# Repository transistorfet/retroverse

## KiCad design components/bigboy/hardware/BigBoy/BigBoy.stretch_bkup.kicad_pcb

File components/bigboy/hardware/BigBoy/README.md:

BigBoy
======

Status: Built & Tested but with design issues (see errata)

Latest: Rev. 1

### About

A generic card with an STM32H7 microcontroller on it that interfaces to the VME bus using GPIO.
I had intended to use it as a bus analyzer, but it's a bit too slow for the k30p CPU at 12.5MHz.

The logo is of [Bronson the Cat](https://www.instagram.com/iambronsoncat/?hl=en)

[Revision 1 Notes & Errata](revisions/BigBoy-rev1-errata.txt)

[Revision 1 Schematic](revisions/BigBoy-rev1.pdf)

[Revision 1 Gerbers](revisions/BigBoy-rev1.zip)

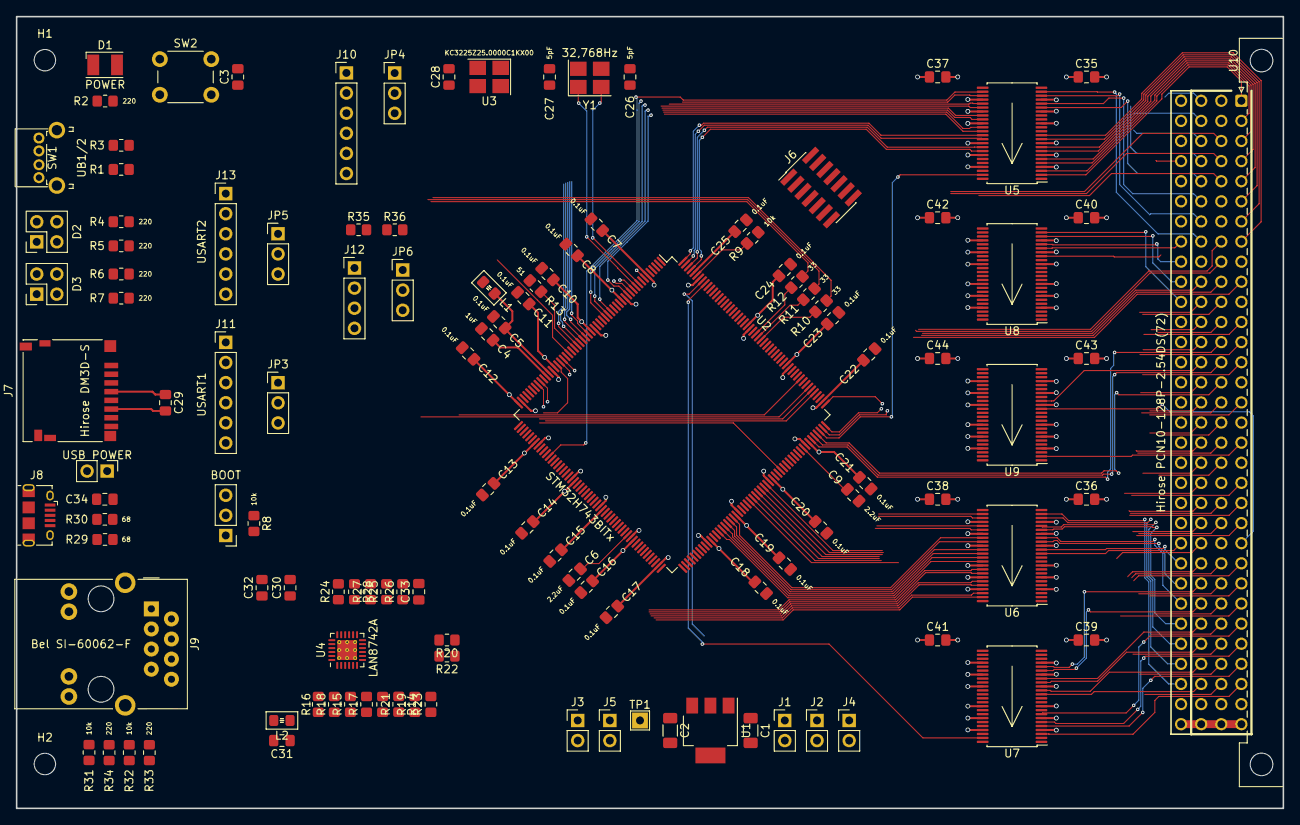
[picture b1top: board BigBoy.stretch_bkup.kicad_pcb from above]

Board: 4 copper layers, 160.0 x 100.0 mm, 120 parts (0 on the bottom side), 282 nets.

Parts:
C1, C2: 4.7uF; C_1206_3216Metric_Pad1.33x1.80mm_HandSolder
C3, C5, C7, C8, C10, C11, C12, C13, C14, C15, C16, C17, C18, C19, C20, C21, C22, C23, C24, C25, C28, C29, C30, C31, C32, C34, C35, C36, C37, C38, C39, C40, C41, C42, C43, C44: 0.1uF; C_0805_2012Metric_Pad1.18x1.45mm_HandSolder
C4: 1uF; C_0805_2012Metric_Pad1.18x1.45mm_HandSolder
C6, C9: 2.2uF; C_0805_2012Metric_Pad1.18x1.45mm_HandSolder
C26, C27: 5pF; C_0805_2012Metric_Pad1.18x1.45mm_HandSolder
C33: 10uF; C_0805_2012Metric_Pad1.18x1.45mm_HandSolder
D1: POWER; LED_PLCC-2_3.4x3.0mm_KA
D2: Dialight 5530188F; Dialight 553-0xxxF
D3: Dialight 5530177F; Dialight 553-0xxxF
H1, H2: MountingHole; MountingHole_2.7mm_M2.5_DIN965
J1, J2, J4: 5V; PinHeader_1x02_P2.54mm_Vertical
J3, J5: 3.3V; PinHeader_1x02_P2.54mm_Vertical
J6: Conn_ST_STDC14; PinHeader_2x07_P1.27mm_Vertical_SMD
J7: Hirose DM3D-S; microSD_HC_Hirose_DM3D-SF
J8: Amphenol 10118194-0001LF; USB_Micro-B_Amphenol_10118194_Horizontal
J9: Bel SI-60062-F; RJ45_Bel_SI-60062-F
J10: SPI2; PinHeader_1x06_P2.54mm_Vertical
J11: USART1; PinHeader_1x06_P2.54mm_Vertical
J12: I^{2}C1; PinHeader_1x04_P2.54mm_Vertical
J13: USART2; PinHeader_1x06_P2.54mm_Vertical
JP1: BOOT; PinHeader_1x03_P2.54mm_Vertical
JP2: USB POWER; PinHeader_1x02_P2.54mm_Vertical
JP3: USART1; PinHeader_1x03_P2.54mm_Vertical
JP4: SPI1; PinHeader_1x03_P2.54mm_Vertical
JP5: USART2; PinHeader_1x03_P2.54mm_Vertical
JP6: I^{2}C1; PinHeader_1x03_P2.54mm_Vertical
L1, L2: 600Ω @ 100MHz (MI0805K601R-10); Ferrite_0805_2012Metric_Pad1.15x1.40mm_BigPads
R1, R3, R8, R9, R14, R15, R16, R21, R22, R31, R32: 10k; R_0805_2012Metric_Pad1.20x1.40mm_HandSolder
R2, R4, R5, R6, R7, R33, R34: 220; R_0805_2012Metric_Pad1.20x1.40mm_HandSolder
R10, R11, R12, R17, R18, R19, R20: 33; R_0805_2012Metric_Pad1.20x1.40mm_HandSolder
R13: 51; R_0805_2012Metric_Pad1.20x1.40mm_HandSolder
R23: 1.5k; R_0805_2012Metric_Pad1.20x1.40mm_HandSolder
R24: 12.1k; R_0805_2012Metric_Pad1.20x1.40mm_HandSolder
R25, R26, R27, R28: 50; R_0805_2012Metric_Pad1.20x1.40mm_HandSolder
R29, R30: 68; R_0805_2012Metric_Pad1.20x1.40mm_HandSolder
R35, R36: 4.7k; R_0805_2012Metric_Pad1.20x1.40mm_HandSolder
SW1: UB1/2; E-Switch TL2243
SW2: ~{RESET}; SW_PUSH_6mm
TP1: 3.3V; TestPoint_THTPad_2.0x2.0mm_Drill1.0mm
U1: AP7361EA-33E-13; SOT-223
U2: STM32H743BITx; LQFP-208_28x28mm_P0.5mm
U3: KC3225Z25.0000C1KX00; Crystal_SMD_3225-4Pin_3.2x2.5mm_HandSoldering
U4: LAN8742A; VQFN-24-1EP_4x4mm_P0.5mm_EP2.5x2.5mm_ThermalVias
U5, U6, U7, U8, U9: 74ALVC16245DG; TSSOP-48_6.1x12.5mm_P0.5mm
U10: Hirose PCN10-128P-2.54DS(72); DIN41612_C_4x32_Male_Horizontal_THT
Y1: 32,768Hz; Crystal_SMD_3225-4Pin_3.2x2.5mm_HandSoldering

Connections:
+3.3V: C2.1, C7.1, C8.1, C10.1, C11.1, C12.1, C13.1, C14.1, C15.1, C16.1, C17.1, C18.1, C19.1, C20.1, C21.1, C22.1, C23.1, C24.1, C25.1, C28.1, C29.1, C30.1, C37.1, C38.1, C41.1, C42.1, C44.1, J3.1, J5.1, J6.3 (VCC), J7.4 (VDD), JP3.3 (B), JP4.3 (B), JP5.3 (B), JP6.3 (B), L1.2, L2.2, R1.1, R2.1, R3.1, R8.1, R9.1, R15.1, R16.1, R21.1, R22.1, R23.1, TP1.1, U1.3 (VO), U2.6 (VBAT), U2.15 (VDD), U2.26 (VDD), U2.39 (VDD), U2.52 (VDD), U2.59 (VDD), U2.73 (VDD), U2.83 (VDD), U2.94 (VDD), U2.103 (VDD), U2.115 (VDD), U2.124 (VDD), U2.137 (VDD33_USB), U2.150 (VDD), U2.158 (VDD), U2.171 (VDD), U2.185 (VDD), U2.204 (VDD), U3.1 (INH), U3.4 (VCC), U4.9 (VDDIO), U5.31 (VCCa), U5.42 (VCCa), U6.31 (VCCa), U6.42 (VCCa), U7.31 (VCCa), U7.42 (VCCa), U8.31 (VCCa), U8.42 (VCCa), U9.31 (VCCa), U9.42 (VCCa)
+5V: C1.1, C34.1, C35.2, C36.2, C39.2, C40.2, C43.2, J1.1, J2.1, J4.1, JP2.1 (A), JP3.1 (A), JP4.1 (A), JP5.1 (A), JP6.1 (A), U1.1 (VI), U5.7 (VCCb), U5.18 (VCCb), U6.7 (VCCb), U6.18 (VCCb), U7.7 (VCCb), U7.18 (VCCb), U8.7 (VCCb), U8.18 (VCCb), U9.7 (VCCb), U9.18 (VCCb), U10.a32 (+5V), U10.b32 (+5V), U10.c32 (+5V), U10.d1 (+5V), U10.d13 (+5V), U10.d32 (+5V)
/IO/RD+: J9.4 (RD+), R27.2, U4.23 (RXP)
/IO/RD-: J9.6 (RD-), R28.2, U4.22 (RXN)
/IO/TD+: J9.1 (TD+), R25.2, U4.21 (TXP)
/IO/TD-: J9.3 (TD-), R26.2, U4.20 (TXN)
AH_DIR: U2.54 (PA5), U6.24 (DIR2)
AL_DIR: U2.55 (PA6), U5.1 (DIR1), U5.24 (DIR2), U6.1 (DIR1)
CLK_25M: R13.2, U3.3 (CLK), U4.5 (XTAL1/CLKIN)
DH_DIR: U2.62 (PB1), U8.1 (DIR1), U8.24 (DIR2)
DL_DIR: U2.63 (PB2), U7.1 (DIR1), U7.24 (DIR2)
GND: C1.2, C2.2, C3.2, C4.1, C5.1, C6.2, C7.2, C8.2, C9.2, C10.2, C11.2, C12.2, C13.2, C14.2, C15.2, C16.2, C17.2, C18.2, C19.2, C20.2, C21.2, C22.2, C23.2, C24.2, C25.2, C26.2, C27.2, C28.2, C29.2, C30.2, C31.2, C32.2, C33.2, C34.2, C35.1, C36.1, C37.2, C38.2, C39.1, C40.1, C41.2, C42.2, C43.1, C44.2, D1.1 (K), D2.1 (A1), D2.3 (A2), D3.1 (A1), D3.3 (A2), J1.2, J2.2, J3.2, J4.2, J5.2, J6.5 (GND), J6.7 (GND), J6.11 (GNDDetect), J7.6 (VSS), J7.10 (SHIELD), J8.5 (GND), J8.6 (Shield), J9.8, J9.SH, J10.2, J11.6, J12.2, J13.6, JP1.3 (B), R14.2, R24.2, R31.2, R32.2, R33.2, R34.2, SW1.1 (C), SW1.3 (C), SW2.1, U1.2 (GND), U2.14 (VSS), U2.25 (VSS), U2.40 (VSSA), U2.51 (VSS), U2.60 (VSS), U2.72 (VSS), U2.82 (VSS), U2.93 (VSS), U2.114 (VSS), U2.125 (VSS), U2.136 (VSS), U2.149 (VSS), U2.170 (VSS), U2.184 (VSS), U2.202 (VSS), U3.2 (GND), U4.25 (VSS), U5.4 (GND), U5.10 (GND), U5.15 (GND), U5.21 (GND), U5.28 (GND), U5.34 (GND), U5.39 (GND), U5.45 (GND), U6.4 (GND), U6.10 (GND), U6.15 (GND), U6.21 (GND), U6.28 (GND), U6.34 (GND), U6.39 (GND), U6.45 (GND), U7.4 (GND), U7.10 (GND), U7.15 (GND), U7.21 (GND), U7.28 (GND), U7.34 (GND), U7.39 (GND), U7.45 (GND), U8.4 (GND), U8.10 (GND), U8.15 (GND), U8.21 (GND), U8.28 (GND), U8.34 (GND), U8.39 (GND), U8.45 (GND), U9.4 (GND), U9.10 (GND), U9.15 (GND), U9.21 (GND), U9.28 (GND), U9.34 (GND), U9.39 (GND), U9.45 (GND), U10.a9 (GND), U10.a11 (GND), U10.a15 (GND), U10.a17 (GND), U10.a19 (GND), U10.b20 (GND), U10.b23 (GND), U10.c9 (GND), U10.d2 (GND), U10.d12 (GND), U10.d22 (GND), U10.d31 (GND)
I2C_SCL: J12.3, R35.2, U2.198 (PB8)
I2C_SDA: J12.4, R36.2, U2.199 (PB9)
LA0: U2.200 (PE0), U7.47 (A0)
LA1: U2.201 (PE1), U7.46 (A1)
LA2: U2.1 (PE2), U7.44 (A2)
LA3: U2.2 (PE3), U7.43 (A3)
LA4: U2.3 (PE4), U7.41 (A4)
LA5: U2.4 (PE5), U7.40 (A5)
LA6: U2.5 (PE6), U7.38 (A6)
LA7: U2.79 (PE7), U7.37 (A7)
LA8: U2.80 (PE8), U7.36 (A8)
LA9: U2.81 (PE9), U7.35 (A9)
LA10: U2.84 (PE10), U7.33 (A10)
LA11: U2.85 (PE11), U7.32 (A11)
LA12: U2.86 (PE12), U7.30 (A12)
LA13: U2.87 (PE13), U7.29 (A13)
LA14: U2.88 (PE14), U7.27 (A14)
LA15: U2.89 (PE15), U7.26 (A15)
LA16: U2.16 (PF0), U8.47 (A0)
LA17: U2.17 (PF1), U8.46 (A1)
LA18: U2.18 (PF2), U8.44 (A2)
LA19: U2.22 (PF3), U8.43 (A3)
LA20: U2.23 (PF4), U8.41 (A4)
LA21: U2.24 (PF5), U8.40 (A5)
LA22: U2.27 (PF6), U8.38 (A6)
LA23: U2.28 (PF7), U8.37 (A7)
LA24: U2.29 (PF8), U8.36 (A8)
LA25: U2.30 (PF9), U8.35 (A9)
LA26: U2.31 (PF10), U8.33 (A10)
LA27: U2.70 (PF11), U8.32 (A11)
LA28: U2.71 (PF12), U8.30 (A12)
LA29: U2.74 (PF13), U8.29 (A13)
LA30: U2.75 (PF14), U8.27 (A14)
LA31: U2.76 (PF15), U8.26 (A15)
LAM0: U2.132 (PG5), U9.40 (A5)
LAM1: U2.133 (PG6), U9.38 (A6)
LAM2: U2.134 (PG7), U9.37 (A7)
LAM3: U2.135 (PG8), U9.36 (A8)
LAM4: U2.178 (PG9), U9.35 (A9)
LAM5: U2.179 (PG10), U9.33 (A10)
LD0: U2.154 (PI0), U5.47 (A0)
LD1: U2.155 (PI1), U5.46 (A1)
LD2: U2.156 (PI2), U5.44 (A2)
LD3: U2.157 (PI3), U5.43 (A3)
LD4: U2.205 (PI4), U5.41 (A4)
LD5: U2.206 (PI5), U5.40 (A5)
LD6: U2.207 (PI6), U5.38 (A6)
LD7: U2.208 (PI7), U5.37 (A7)
LD8: U2.7 (PI8), U5.36 (A8)
LD9: U2.11 (PI9), U5.35 (A9)
LD10: U2.12 (PI10), U5.33 (A10)
LD11: U2.13 (PI11), U5.32 (A11)
LD12: U2.19 (PI12), U5.30 (A12)
LD13: U2.20 (PI13), U5.29 (A13)
LD14: U2.21 (PI14), U5.27 (A14)
LD15: U2.64 (PI15), U5.26 (A15)
LD16: U2.65 (PJ0), U6.47 (A0)
LD17: U2.66 (PJ1), U6.46 (A1)
LD18: U2.67 (PJ2), U6.44 (A2)
LD19: U2.68 (PJ3), U6.43 (A3)
LD20: U2.69 (PJ4), U6.41 (A4)
LD21: U2.95 (PJ5), U6.40 (A5)
LD22: U2.118 (PJ6), U6.38 (A6)
LD23: U2.119 (PJ7), U6.37 (A7)
LD24: U2.120 (PJ8), U6.36 (A8)
LD25: U2.121 (PJ9), U6.35 (A9)
LD26: U2.122 (PJ10), U6.33 (A10)
LD27: U2.123 (PJ11), U6.32 (A11)
LD28: U2.174 (PJ12), U6.30 (A12)
LD29: U2.175 (PJ13), U6.29 (A13)
LD30: U2.176 (PJ14), U6.27 (A14)
LD31: U2.177 (PJ15), U6.26 (A15)
unnamed: C6.1, U2.92 (VCAP)
unnamed: C9.1, U2.148 (VCAP)
unnamed: D1.2 (A), R2.2
unnamed: D2.2 (K1), R4.2
unnamed: D2.4 (K2), R5.2
unnamed: D3.2 (K1), R6.2
unnamed: D3.4 (K2), R7.2
unnamed: J8.3 (D+), R29.1
unnamed: J8.2 (D-), R30.1
unnamed: J8.1 (VBUS), JP2.2 (B)
unnamed: J9.L2, R34.1
unnamed: J9.L4, R33.1
unnamed: C32.1, C33.1, J9.2 (TCT), J9.5 (RCT), L2.1, R25.1, R26.1, R27.1, R28.1, U4.1 (VDD2A), U4.19 (VDD1A)
unnamed: J10.1, JP4.2 (C)
unnamed: J11.4, JP3.2 (C)
unnamed: J12.1, JP6.2 (C), R35.1, R36.1
unnamed: J13.4, JP5.2 (C)
unnamed: JP1.1 (A), R8.2
unnamed: JP1.2 (C), U2.197 (BOOT0)
unnamed: C26.1, U2.9 (PC14), Y1.2
unnamed: C27.1, U2.10 (PC15), Y1.1
unnamed: R10.1, U2.180 (PG11)
unnamed: R11.1, U2.181 (PG12)
unnamed: R12.1, U2.182 (PG13)
unnamed: R13.1, U2.32 (PH0)
unnamed: R9.2, U2.203 (PDR_ON)
unnamed: C4.2, C5.2, L1.1, U2.41 (VREF+), U2.42 (VDDA)
unnamed: R19.2, R21.2, U4.11 (CRS_DV/MODE2)
unnamed: J9.L1, R31.1, U4.3 (LED1/REGOFF)
unnamed: R24.1, U4.24 (RBIAS)
unnamed: R15.2, R17.2, U4.8 (RXD0/MODE0)
unnamed: R16.2, R18.2, U4.7 (RXD1/MODE1)
unnamed: R14.1, U4.10 (RXER/PHYAD0)
unnamed: C31.1, U4.6 (VDDCR)
unnamed: R20.2, R22.2, U4.14 (~INT/REFCLKO)
RMII_CRS_DV: R19.1, U2.56 (PA7)
RMII_MDC: U2.36 (PC1), U4.13 (MDC)
RMII_MDIO: R23.2, U2.45 (PA2), U4.12 (MDIO)
RMII_REF_CLK: R20.1, U2.44 (PA1)
RMII_RXD0: R17.1, U2.57 (PC4)
RMII_RXD1: R18.1, U2.58 (PC5)
RMII_TXD0: R12.2, U4.17 (TXD0)
RMII_TXD1: R11.2, U4.18 (TXD1)
RMII_TXEN: R10.2, U4.16 (TXEN)
RMII_nINT: J9.L3, R32.1, U2.37 (PC2_C), U4.2 (LED2/~INTSEL)
SDIO_CLK: J7.5 (CLK), U2.163 (PC12)
SDIO_CMD: J7.3 (CMD), U2.166 (PD2)
SDIO_D0: J7.7 (DAT0), U2.140 (PC8)
SDIO_D1: J7.8 (DAT1), U2.141 (PC9)
SDIO_D2: J7.1 (DAT2), U2.161 (PC10)
SDIO_D3: J7.2 (DAT3/CD), U2.162 (PC11)
SDIO_DET: J7.9 (DET), U2.38 (PC3_C)
SPI_SCK: J10.5, U2.105 (PB13)
SPI_SDI: J10.4, U2.107 (PB15)
SPI_SDO: J10.3, U2.106 (PB14)
TCK/SWCLK: J6.6 (JCLK/SWCLK), U2.159 (PA14)
TDI: J6.10 (JTDI/NC), U2.160 (PA15)
TDO/SWO: J6.8 (JTDO/SWO), U2.192 (PB3)
TMS/SWDIO: J6.4 (JTMS/SWDIO), U2.147 (PA13)
UB1: R1.2, SW1.2 (D), U2.143 (PA9)
UB2: R3.2, SW1.4 (D), U2.110 (PD10)
UL1: R4.1, U2.35 (PC0)
UL2: R5.1, U2.138 (PC6)
UL3: R6.1, U2.139 (PC7)
UL4: R7.1, U2.8 (PC13)
USART1_CTS: J11.1, U2.111 (PD11)
USART1_RTS: J11.5, U2.112 (PD12)
USART1_RX: J11.3, U2.109 (PD9)
USART1_TX: J11.2, U2.108 (PD8)
USART2_CTS: J13.1, U2.167 (PD3)
USART2_RTS: J13.5, U2.168 (PD4)
USART2_RX: J13.3, U2.172 (PD6)
USART2_TX: J13.2, U2.169 (PD5)
USB_DN: R30.2, U2.145 (PA11)
USB_DP: R29.2, U2.146 (PA12)
USB_ID: J8.4 (ID), U2.144 (PA10)
VA1: U7.3 (B1), U10.a30 (A01)
VA2: U7.5 (B2), U10.a29 (A02)
VA3: U7.6 (B3), U10.a28 (A03)
VA4: U7.8 (B4), U10.a27 (A04)
VA5: U7.9 (B5), U10.a26 (A05)
VA6: U7.11 (B6), U10.a25 (A06)
VA7: U7.12 (B7), U10.a24 (A07)
VA8: U7.13 (B8), U10.c30 (A8)
VA9: U7.14 (B9), U10.c29 (A9)
VA10: U7.16 (B10), U10.c28 (A10)
VA11: U7.17 (B11), U10.c27 (A11)
VA12: U7.19 (B12), U10.c26 (A12)
VA13: U7.20 (B13), U10.c25 (A13)
VA14: U7.22 (B14), U10.c24 (A14)
VA15: U7.23 (B15), U10.c23 (A15)
VA16: U8.2 (B0), U10.c22 (A16)
VA17: U8.3 (B1), U10.c21 (A17)
VA18: U8.5 (B2), U10.c20 (A18)
VA19: U8.6 (B3), U10.c19 (A19)
VA20: U8.8 (B4), U10.c18 (A20)
VA21: U8.9 (B5), U10.c17 (A21)
VA22: U8.11 (B6), U10.c16 (A22)
VA23: U8.12 (B7), U10.c15 (A23)
VA24: U8.13 (B8), U10.d4 (A24)
VA25: U8.14 (B9), U10.d5 (A25)
VA26: U8.16 (B10), U10.d6 (A26)
VA27: U8.17 (B11), U10.d7 (A27)
VA28: U8.19 (B12), U10.d8 (A28)
VA29: U8.20 (B13), U10.d9 (A29)
VA30: U8.22 (B14), U10.d10 (A30)
VA31: U8.23 (B15), U10.d11 (A31)
VAM0: U9.9 (B5), U10.b16 (AM0)
VAM1: U9.11 (B6), U10.b17 (AM1)
VAM2: U9.12 (B7), U10.b18 (AM2)
VAM3: U9.13 (B8), U10.b19 (AM3)
VAM4: U9.14 (B9), U10.a23 (AM4)
VAM5: U9.16 (B10), U10.c14 (AM5)
VCP_RX: J6.13 (VCP_RX), U2.196 (PB7)
VCP_TX: J6.14 (VCP_TX), U2.195 (PB6)
VD0: U5.2 (B0), U10.a1 (D00)
VD1: U5.3 (B1), U10.a2 (D01)
VD2: U5.5 (B2), U10.a3 (D02)
VD3: U5.6 (B3), U10.a4 (D03)
VD4: U5.8 (B4), U10.a5 (D04)
VD5: U5.9 (B5), U10.a6 (D05)
VD6: U5.11 (B6), U10.a7 (D06)
VD7: U5.12 (B7), U10.a8 (D07)
VD8: U5.13 (B8), U10.c1 (D08)
VD9: U5.14 (B9), U10.c2 (D09)
VD10: U5.16 (B10), U10.c3 (D10)
VD11: U5.17 (B11), U10.c4 (D11)
VD12: U5.19 (B12), U10.c5 (D12)
VD13: U5.20 (B13), U10.c6 (D13)
VD14: U5.22 (B14), U10.c7 (D14)
VD15: U5.23 (B15), U10.c8 (D15)
VD16: U6.2 (B0), U10.d14 (D16)
VD17: U6.3 (B1), U10.d15 (D17)
VD18: U6.5 (B2), U10.d16 (D18)
VD19: U6.6 (B3), U10.d17 (D19)
VD20: U6.8 (B4), U10.d18 (D20)
VD21: U6.9 (B5), U10.d19 (D21)
VD22: U6.11 (B6), U10.d20 (D22)
VD23: U6.12 (B7), U10.d21 (D23)
VD24: U6.13 (B8), U10.d23 (D24)
VD25: U6.14 (B9), U10.d24 (D25)
VD26: U6.16 (B10), U10.d25 (D26)
VD27: U6.17 (B11), U10.d26 (D27)
VD28: U6.19 (B12), U10.d27 (D28)
VD29: U6.20 (B13), U10.d28 (D29)
VD30: U6.22 (B14), U10.d29 (D30)
VD31: U6.23 (B15), U10.d30 (D31)
~AH_OE: U2.50 (PA3), U6.25 (~OE2)
~AL_OE: U2.53 (PA4), U5.25 (~OE2), U5.48 (~OE1), U6.48 (~OE1)
~CTRL_DIR: U2.194 (PB5), U9.1 (DIR1), U9.24 (DIR2)
~CTRL_OE: U2.193 (PB4), U9.25 (~OE2), U9.48 (~OE1)
~DH_OE: U2.142 (PA8), U8.25 (~OE2), U8.48 (~OE1)
~DL_OE: U2.61 (PB0), U7.25 (~OE2), U7.48 (~OE1)
~LAS: U2.77 (PG0), U9.47 (A0)
~LDS0: U2.129 (PG2), U9.44 (A2)
~LDS1: U2.78 (PG1), U9.46 (A1)
~LLWORD: U2.131 (PG4), U9.41 (A4)
~LWRITE: U2.130 (PG3), U9.43 (A3)
~RESET: C3.1, J6.12 (~RST), SW2.2, U2.34 (NRST), U4.15 (~RST)
~SPI_CS: J10.6, U2.104 (PB12)
~VACFAIL: U2.113 (PD13), U10.b3 (~ACFAIL)
~VAS: U9.2 (B0), U10.a18 (~AS)
~VBBSY: U2.46 (PH2), U10.b1 (~BBSY)
~VBCLR: U2.47 (PH3), U10.b2 (~BCLR)
~VBERR: U2.191 (PG15), U10.c11 (~BERR)
~VBG0IN: U2.48 (PH4), U10.b4 (~BG0IN)
~VBG0OUT: U2.49 (PH5), U10.b5 (~BG0OUT)
~VBG1IN: U2.96 (PH6), U10.b6 (~BG1IN)
~VBG1OUT: U2.97 (PH7), U10.b7 (~BG1OUT)
~VBG2IN: U2.98 (PH8), U10.b8 (~BG2IN)
~VBG2OUT: U2.99 (PH9), U10.b9 (~BG2OUT)
~VBG3IN: U2.100 (PH10), U10.b10 (~BG3IN)
~VBG3OUT: U2.101 (PH11), U10.b11 (~BG3OUT)
~VBR0: U2.102 (PH12), U10.b12 (~BR0)
~VBR1: U2.151 (PH13), U10.b13 (~BR1)
~VBR2: U2.152 (PH14), U10.b14 (~BR2)
~VBR3: U2.153 (PH15), U10.b15 (~BR3)
~VDS0: U9.5 (B2), U10.a13 (~DS0)
~VDS1: U9.3 (B1), U10.a12 (~DS1)
~VDTACK: U2.183 (PG14), U10.a16 (~DTACK)
~VIACKIN: U2.164 (PD0), U10.a21 (~IACKIN)
~VIACKOUT: U2.165 (PD1), U10.a22 (~IACKOUT)
~VIACK: U2.126 (PK0), U10.a20 (~IACK)
~VIRQ1: U2.127 (PK1), U10.b30 (~IRQ1)
~VIRQ2: U2.128 (PK2), U10.b29 (~IRQ2)
~VIRQ3: U2.186 (PK3), U10.b28 (~IRQ3)
~VIRQ4: U2.187 (PK4), U10.b27 (~IRQ4)
~VIRQ5: U2.188 (PK5), U10.b26 (~IRQ5)
~VIRQ6: U2.189 (PK6), U10.b25 (~IRQ6)
~VIRQ7: U2.190 (PK7), U10.b24 (~IRQ7)
~VLWORD: U9.8 (B4), U10.c13 (~LWORD)
~VRETRY: U2.173 (PD7), U10.d3 (~RETRY)
~VSERCLK: U2.90 (PB10), U10.b21 (SERCLK)
~VSERDAT: U2.91 (PB11), U10.b22 (SERDAT)
~VSYSCLK: U2.117 (PD15), U10.a10 (SYSCLK)
~VSYSFAIL: U2.116 (PD14), U10.c10 (~SYSFAIL)
~VSYSRESET: U2.43 (PA0), U10.c12 (~SYSRESET)
~VWRITE: U9.6 (B3), U10.a14 (~WRITE)

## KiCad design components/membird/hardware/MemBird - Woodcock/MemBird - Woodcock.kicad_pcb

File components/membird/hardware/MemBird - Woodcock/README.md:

MemBird - Woodcock
==================

Status: Built & Tested

Latest: Rev. 1

### About

A 16-bit VME memory card with 4MB of Static RAM at either 5V or 3.3V

It's named after the American Woodcock, a small bird that moves along with a slow rhythmic walk,
since this card only has a small amount of memory, and will be slower to access, being only 16-bits.

They are very cute birds, with an adorable walk, and a funny call
https://www.youtube.com/watch?v=fpCO6CUH8Zc
https://www.youtube.com/watch?v=97nnyyvXzmA

[Revision 1 Notes & Errata](revisions/MemBird%20-%20Woodcock-rev1-errata.txt)

[Revision 1 Schematic](revisions/MemBird%20-%20Woodcock-rev1.pdf)

[Revision 1 Gerbers](revisions/MemBird%20-%20Woodcock-rev1.zip)

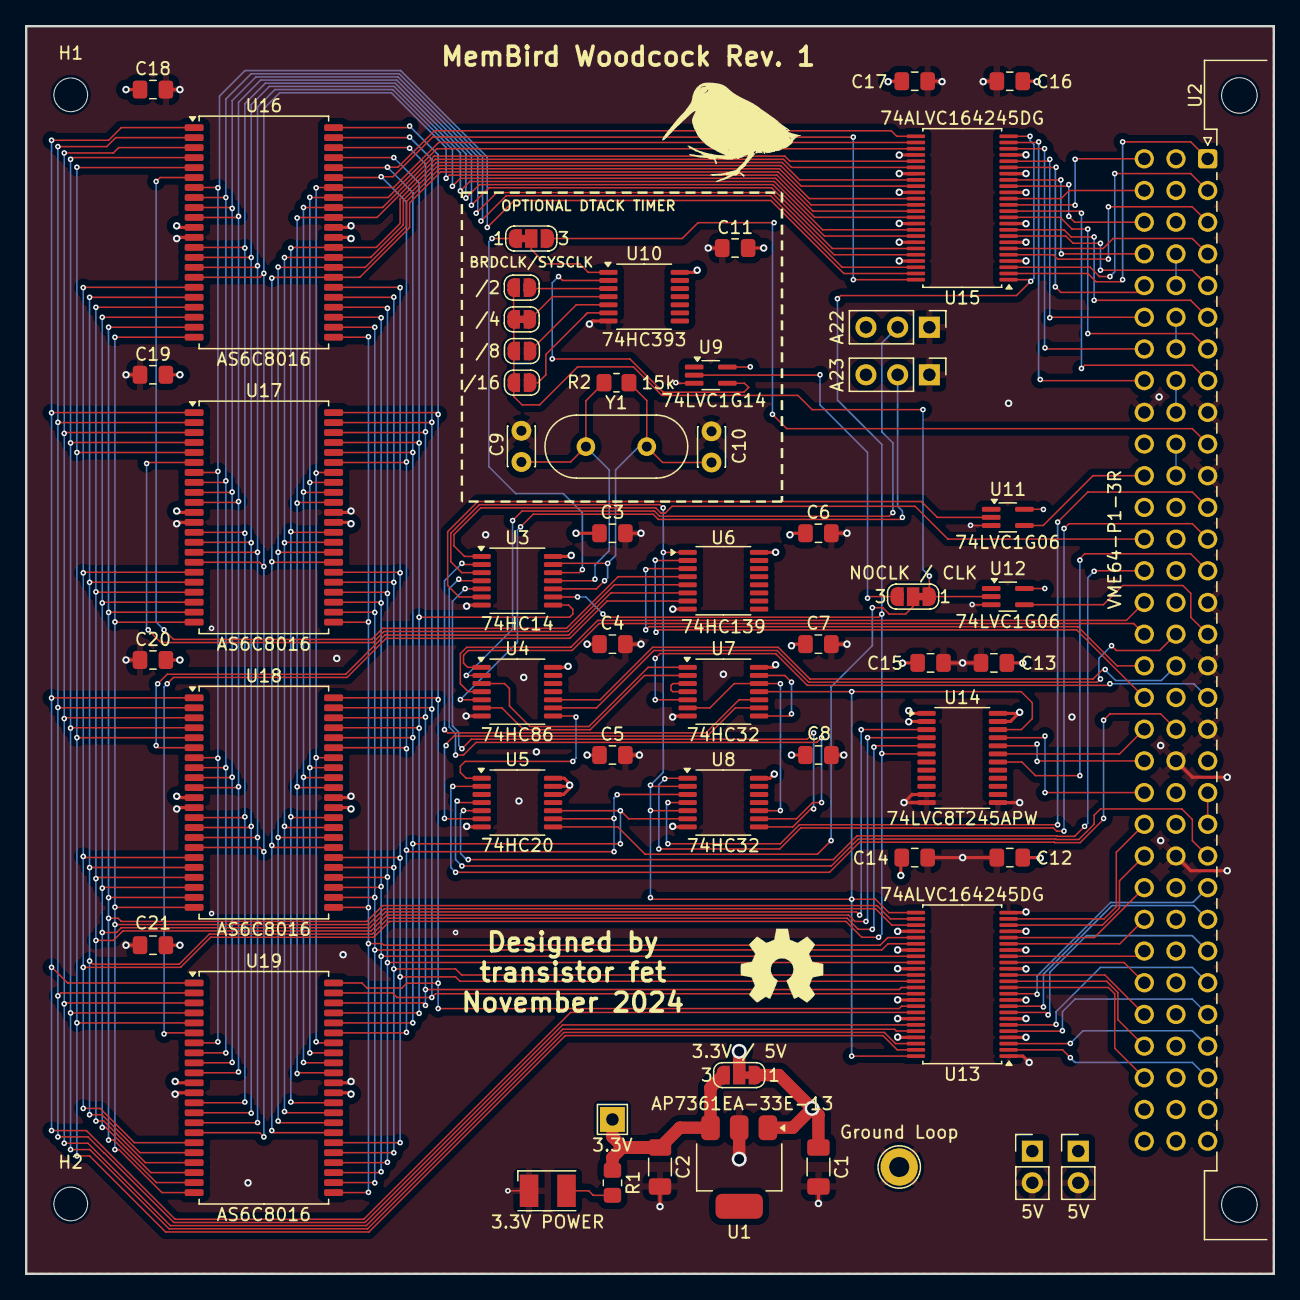
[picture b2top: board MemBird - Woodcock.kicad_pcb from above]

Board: 4 copper layers, 100.0 x 100.0 mm, 60 parts (0 on the bottom side), 131 nets.

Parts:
C1, C2: 4.7uF; C_1206_3216Metric_Pad1.33x1.80mm_HandSolder
C3, C4, C5, C6, C7, C8, C11, C12, C13, C14, C15, C16, C17, C18, C19, C20, C21: 0.1uF; C_0805_2012Metric_Pad1.18x1.45mm_HandSolder
C9, C10: 18pF; C_Disc_D3.0mm_W2.0mm_P2.50mm
D1: 3.3V POWER; LED_PLCC-2_3.4x3.0mm_KA
H1, H2: MountingHole; MountingHole_2.7mm_M2.5_DIN965
J2, J3: 5V; PinHeader_1x02_P2.54mm_Vertical
JP1: 3.3V / 5V; SolderJumper-3_P1.3mm_Bridged12_RoundedPad1.0x1.5mm_NumberL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
JP2: A23; PinHeader_1x03_P2.54mm_Vertical
JP3: A22; PinHeader_1x03_P2.54mm_Vertical
JP4: NOCLK / CLK; SolderJumper-3_P1.3mm_Bridged12_RoundedPad1.0x1.5mm_NumberL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
JP5: BRDCLK/SYSCLK; SolderJumper-3_P1.3mm_Bridged12_RoundedPad1.0x1.5mm_NumberL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
JP6: /2; SolderJumper-2_P1.3mm_Open_RoundedPad1.0x1.5mm
JP7: /4; SolderJumper-2_P1.3mm_Bridged_RoundedPad1.0x1.5mm
JP8: /8; SolderJumper-2_P1.3mm_Open_RoundedPad1.0x1.5mm
JP9: /16; SolderJumper-2_P1.3mm_Open_RoundedPad1.0x1.5mm
R1: 220; R_0805_2012Metric_Pad1.20x1.40mm_HandSolder
R2: 15k; R_0805_2012Metric_Pad1.20x1.40mm_HandSolder
S1: Logo_Open_Hardware_Small; OSHW-Symbol_6.7x6mm_SilkScreen
TP1: Ground Loop; TestPoint_Loop_D2.60mm_Drill1.6mm_Beaded
TP2: 3.3V; TestPoint_THTPad_2.0x2.0mm_Drill1.0mm
U1: AP7361EA-33E-13; SOT-223
U2: VME64-P1-3R; DIN41612_C_3x32_Male_Horizontal_THT
U3: 74HC14; TSSOP-14_4.4x5mm_P0.65mm
U4: 74HC86; TSSOP-14_4.4x5mm_P0.65mm
U5: 74HC20; TSSOP-14_4.4x5mm_P0.65mm
U6: 74HC139; TSSOP-16_4.4x5mm_P0.65mm
U7, U8: 74HC32; TSSOP-14_4.4x5mm_P0.65mm
U9: 74LVC1G14; SOT-353_SC-70-5_Handsoldering
U10: 74HC393; TSSOP-14_4.4x5mm_P0.65mm
U11, U12: 74LVC1G06; SOT-353_SC-70-5_Handsoldering
U13, U15: 74ALVC164245DG; TSSOP-48_6.1x12.5mm_P0.5mm
U14: 74LVC8T245APW; TSSOP-24_4.4x7.8mm_P0.65mm
U16, U17, U18, U19: AS6C8016; TSOP-II-44_10.16x18.41mm_P0.8mm
Y1: Crystal; Crystal_HC49-4H_Vertical

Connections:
+3.3V: C2.1, JP1.3 (B), R1.1, TP2.1, U1.3 (VO)
GND: C1.2, C2.2, C3.2, C4.2, C5.2, C6.2, C7.2, C8.2, C9.2, C10.2, C11.2, C12.1, C13.1, C14.2, C15.2, C16.1, C17.2, C18.2, C19.2, C20.2, C21.2, D1.1 (K), J2.2, J3.2, JP2.1 (A), JP3.1 (A), TP1.1, U1.2 (GND), U2.a9 (GND), U2.a11 (GND), U2.a15 (GND), U2.a17 (GND), U2.a19 (GND), U2.b20 (GND), U2.b23 (GND), U2.c9 (GND), U3.7 (GND), U4.7 (GND), U5.7 (GND), U6.8 (GND), U7.7 (GND), U8.7 (GND), U9.3, U10.7 (GND), U11.3, U12.3, U13.1 (DIR1), U13.4 (GND), U13.10 (GND), U13.15 (GND), U13.21 (GND), U13.24 (DIR2), U13.28 (GND), U13.34 (GND), U13.39 (GND), U13.45 (GND), U14.2 (DIR), U14.11 (GND), U14.12 (GND), U14.13 (GND), U15.4 (GND), U15.10 (GND), U15.15 (GND), U15.21 (GND), U15.28 (GND), U15.34 (GND), U15.39 (GND), U15.45 (GND), U16.12 (VSS), U16.34 (VSS), U17.12 (VSS), U17.34 (VSS), U18.12 (VSS), U18.34 (VSS), U19.12 (VSS), U19.34 (VSS)
LA1: U13.47 (A0), U16.5 (A0), U17.5 (A0), U18.5 (A0), U19.5 (A0)
LA2: U13.46 (A1), U16.4 (A1), U17.4 (A1), U18.4 (A1), U19.4 (A1)
LA3: U13.44 (A2), U16.3 (A2), U17.3 (A2), U18.3 (A2), U19.3 (A2)
LA4: U13.43 (A3), U16.2 (A3), U17.2 (A3), U18.2 (A3), U19.2 (A3)
LA5: U13.41 (A4), U16.1 (A4), U17.1 (A4), U18.1 (A4), U19.1 (A4)
LA6: U13.40 (A5), U16.44 (A5), U17.44 (A5), U18.44 (A5), U19.44 (A5)
LA7: U13.38 (A6), U16.43 (A6), U17.43 (A6), U18.43 (A6), U19.43 (A6)
LA8: U13.37 (A7), U16.42 (A7), U17.42 (A7), U18.42 (A7), U19.42 (A7)
LA9: U13.36 (A8), U16.28 (A8), U17.28 (A8), U18.28 (A8), U19.28 (A8)
LA10: U13.35 (A9), U16.27 (A9), U17.27 (A9), U18.27 (A9), U19.27 (A9)
LA11: U13.33 (A10), U16.26 (A10), U17.26 (A10), U18.26 (A10), U19.26 (A10)
LA12: U13.32 (A11), U16.25 (A11), U17.25 (A11), U18.25 (A11), U19.25 (A11)
LA13: U13.30 (A12), U16.24 (A12), U17.24 (A12), U18.24 (A12), U19.24 (A12)
LA14: U13.29 (A13), U16.23 (A13), U17.23 (A13), U18.23 (A13), U19.23 (A13)
LA15: U13.27 (A14), U16.22 (A14), U17.22 (A14), U18.22 (A14), U19.22 (A14)
LA16: U13.26 (A15), U16.21 (A15), U17.21 (A15), U18.21 (A15), U19.21 (A15)
LA17: U14.3 (A0), U16.20 (A16), U17.20 (A16), U18.20 (A16), U19.20 (A16)
LA18: U14.4 (A1), U16.19 (A17), U17.19 (A17), U18.19 (A17), U19.19 (A17)
LA19: U14.5 (A2), U16.18 (A18), U17.18 (A18), U18.18 (A18), U19.18 (A18)
LD0: U15.47 (A0), U16.7 (Q0), U17.7 (Q0), U18.7 (Q0), U19.7 (Q0)
LD1: U15.46 (A1), U16.8 (Q1), U17.8 (Q1), U18.8 (Q1), U19.8 (Q1)
LD2: U15.44 (A2), U16.9 (Q2), U17.9 (Q2), U18.9 (Q2), U19.9 (Q2)
LD3: U15.43 (A3), U16.10 (Q3), U17.10 (Q3), U18.10 (Q3), U19.10 (Q3)
LD4: U15.41 (A4), U16.13 (Q4), U17.13 (Q4), U18.13 (Q4), U19.13 (Q4)
LD5: U15.40 (A5), U16.14 (Q5), U17.14 (Q5), U18.14 (Q5), U19.14 (Q5)
LD6: U15.38 (A6), U16.15 (Q6), U17.15 (Q6), U18.15 (Q6), U19.15 (Q6)
LD7: U15.37 (A7), U16.16 (Q7), U17.16 (Q7), U18.16 (Q7), U19.16 (Q7)
LD8: U15.36 (A8), U16.29 (Q8), U17.29 (Q8), U18.29 (Q8), U19.29 (Q8)
LD9: U15.35 (A9), U16.30 (Q9), U17.30 (Q9), U18.30 (Q9), U19.30 (Q9)
LD10: U15.33 (A10), U16.31 (Q10), U17.31 (Q10), U18.31 (Q10), U19.31 (Q10)
LD11: U15.32 (A11), U16.32 (Q11), U17.32 (Q11), U18.32 (Q11), U19.32 (Q11)
LD12: U15.30 (A12), U16.35 (Q12), U17.35 (Q12), U18.35 (Q12), U19.35 (Q12)
LD13: U15.29 (A13), U16.36 (Q13), U17.36 (Q13), U18.36 (Q13), U19.36 (Q13)
LD14: U15.27 (A14), U16.37 (Q14), U17.37 (Q14), U18.37 (Q14), U19.37 (Q14)
LD15: U15.26 (A15), U16.38 (Q15), U17.38 (Q15), U18.38 (Q15), U19.38 (Q15)
unnamed: C9.1, R2.2, U3.11, Y1.1
unnamed: C10.1, R2.1, U3.10, U3.13, Y1.2
unnamed: D1.2 (A), R1.2
unnamed: JP2.2 (C), U4.5
unnamed: JP3.2 (C), U4.2
unnamed: JP4.1 (A), JP6.2 (B), JP7.2 (B), JP8.2 (B), JP9.2 (B), U12.2
unnamed: JP4.3 (B), U9.2
unnamed: JP4.2 (C), U5.8
unnamed: JP5.1 (A), U3.12
unnamed: JP5.2 (C), U10.1 (CP)
unnamed: JP6.1 (A), U10.3 (Q0)
unnamed: JP7.1 (A), U10.4 (Q1)
unnamed: JP8.1 (A), U10.5 (Q2)
unnamed: JP9.1 (A), U10.6 (Q3)
unnamed: U2.a21 (~IACKIN), U2.a22 (~IACKOUT)
unnamed: U2.b4 (~BG0IN), U2.b5 (~BG0OUT)
unnamed: U2.b6 (~BG1IN), U2.b7 (~BG1OUT)
unnamed: U2.b8 (~BG2IN), U2.b9 (~BG2OUT)
unnamed: U2.b10 (~BG3IN), U2.b11 (~BG3OUT)
unnamed: U3.2, U7.10
unnamed: U3.4, U8.9
unnamed: U3.5, U8.8
unnamed: U4.3, U7.1
unnamed: U4.6, U7.2
unnamed: U4.8, U5.1
unnamed: U5.6, U7.9
unnamed: U7.8, U7.13
unnamed: U9.4, U10.2 (MR)
unnamed: U3.6, U11.2
VA1: U2.a30 (A01), U13.2 (B0)
VA2: U2.a29 (A02), U13.3 (B1)
VA3: U2.a28 (A03), U13.5 (B2)
VA4: U2.a27 (A04), U13.6 (B3)
VA5: U2.a26 (A05), U13.8 (B4)
VA6: U2.a25 (A06), U13.9 (B5)
VA7: U2.a24 (A07), U13.11 (B6)
VA8: U2.c30 (A8), U13.12 (B7)
VA9: U2.c29 (A9), U13.13 (B8)
VA10: U2.c28 (A10), U13.14 (B9)
VA11: U2.c27 (A11), U13.16 (B10)
VA12: U2.c26 (A12), U13.17 (B11)
VA13: U2.c25 (A13), U13.19 (B12)
VA14: U2.c24 (A14), U13.20 (B13)
VA15: U2.c23 (A15), U13.22 (B14)
VA16: U2.c22 (A16), U13.23 (B15)
VA17: U2.c21 (A17), U14.21 (B0)
VA18: U2.c20 (A18), U14.20 (B1)
VA19: U2.c19 (A19), U14.19 (B2)
VA20: U2.c18 (A20), U6.2 (A0)
VA21: U2.c17 (A21), U6.3 (A1)
VA22: U2.c16 (A22), U4.1
VA23: U2.c15 (A23), U4.4
VAM0: U2.b16 (AM0), U4.9
VAM1: U2.b17 (AM1), U4.10
VAM3: U2.b19 (AM3), U5.2
VAM4: U2.a23 (AM4), U5.4
VAM5: U2.c14 (AM5), U5.5
VBUS: C1.1, C12.2, C13.2, C16.2, J2.1, J3.1, JP1.1 (A), U1.1 (VI), U2.a32 (+5V), U2.b32 (+5V), U2.c32 (+5V), U11.5, U12.5, U13.7 (VCCb), U13.18 (VCCb), U14.23 (VCCb), U14.24 (VCCb), U15.7 (VCCb), U15.18 (VCCb)
VD0: U2.a1 (D00), U15.2 (B0)
VD1: U2.a2 (D01), U15.3 (B1)
VD2: U2.a3 (D02), U15.5 (B2)
VD3: U2.a4 (D03), U15.6 (B3)
VD4: U2.a5 (D04), U15.8 (B4)
VD5: U2.a6 (D05), U15.9 (B5)
VD6: U2.a7 (D06), U15.11 (B6)
VD7: U2.a8 (D07), U15.12 (B7)
VD8: U2.c1 (D08), U15.13 (B8)
VD9: U2.c2 (D09), U15.14 (B9)
VD10: U2.c3 (D10), U15.16 (B10)
VD11: U2.c4 (D11), U15.17 (B11)
VD12: U2.c5 (D12), U15.19 (B12)
VD13: U2.c6 (D13), U15.20 (B13)
VD14: U2.c7 (D14), U15.22 (B14)
VD15: U2.c8 (D15), U15.23 (B15)
VMEM: C3.1, C4.1, C5.1, C6.1, C7.1, C8.1, C11.1, C14.1, C15.1, C17.1, C18.1, C19.1, C20.1, C21.1, JP1.2 (C), JP2.3 (B), JP3.3 (B), U3.14 (VCC), U4.14 (VCC), U5.12, U5.13, U5.14 (VCC), U6.16 (VCC), U7.14 (VCC), U8.14 (VCC), U9.5, U10.14 (VCC), U13.31 (VCCa), U13.42 (VCCa), U14.1 (VCCa), U15.31 (VCCa), U15.42 (VCCa), U16.11 (VCC), U16.33 (VCC), U17.11 (VCC), U17.33 (VCC), U18.11 (VCC), U18.33 (VCC), U19.11 (VCC), U19.33 (VCC)
~ADDR_SEL: U7.3, U7.4
~ADDR_STROBE: U7.6, U7.12, U8.10
~CS0: U6.4 (O0), U16.6 (~CE)
~CS1: U6.5 (O1), U17.6 (~CE)
~CS2: U6.6 (O2), U18.6 (~CE)
~CS3: U6.7 (O3), U19.6 (~CE)
~CS_ANY: U3.3, U6.1 (E), U7.11, U8.2, U8.5, U13.25 (~OE2), U13.48 (~OE1), U14.22 (~OE)
~LDS: U5.9, U8.3, U15.48 (~OE1), U16.39 (~LB), U17.39 (~LB), U18.39 (~LB), U19.39 (~LB)
~RD: U3.8, U16.41 (~OE), U17.41 (~OE), U18.41 (~OE), U19.41 (~OE)
~SYSCLK: JP5.3 (B), U2.a10 (SYSCLK)
~UDS: U5.10, U8.6, U15.25 (~OE2), U16.40 (~UB), U17.40 (~UB), U18.40 (~UB), U19.40 (~UB)
~VAS: U2.a18 (~AS), U7.5
~VBERR: U2.c11 (~BERR), U11.4
~VDS0: U2.a13 (~DS0), U8.1
~VDS1: U2.a12 (~DS1), U8.4
~VDTACK: U2.a16 (~DTACK), U12.4
~VLWORD: U2.c13 (~LWORD), U3.1
~VWRITE: U2.a14 (~WRITE), U14.18 (B3)
~WR: U3.9, U14.6 (A3), U15.1 (DIR1), U15.24 (DIR2), U16.17 (~WE), U17.17 (~WE), U18.17 (~WE), U19.17 (~WE)
